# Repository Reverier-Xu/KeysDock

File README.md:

# 

The hall-effect powered, high performance, feature riched keyboard!

> [!WARNING]
> **STILL IN EARLY DEVELOPMENT!**
>
> - [ ] PCB design
> - [ ] Suitkit design
> - [ ] Firmware
> - [ ] Software
> - [ ] Extended external controllers

## Keys layout

KeysDock uses main dock with 80-keys ANSI layout.

## Suitkit design

Designed use [FreeCAD](https://www.freecad.org/) for 3D modeling and [QCAD](https://www.qcad.org/) for nameplate drawn.

Fonts used in design:

- [Iosevka](https://typeof.net/Iosevka/): An elegant monospace coding font;
- [Hershey Fonts](https://en.wikipedia.org/wiki/Hershey_fonts): a collection of vector fonts originally designed to be rendered using vectors on early cathode ray tube displays.

## Hardware design

Designed use [KiCAD](https://www.kicad.org/), validated on [QUCS-s](https://ra3xdh.github.io/).

- MCU and BLE/WiFi: ESP32-C6
- ADC: TLA2518
- Hall-effect sensors: SC4823S6-TR
- Magnetic switch: Gateron Low Profile Magnetic Jade Pro Switch

More component info is available under [here](hardware/docs).

> [!WARNING]
> LIMITATIONS: the extended F-keys suite do not have sleep mode, awake functions and RGB lights.
> Hall-effect keyboard requires too many I/O pins, which makes difficulty in transfer additional features to external dock.

## Firmware

Rust 1.94 is required for build firmware.

## Software

WIP...

## Credits

This project is built entirely with opensource softwares, with power of opensource RISC-V instruction-set.

- [KiCAD](https://www.kicad.org): GPLv3
- [FreeCAD](https://www.freecad.org): LGPLv2.1
- [QCAD](https://www.qcad.org): GPLv3
- [Inkscape](https://www.inkscape.org): GPLv2
- [QUCS-s](https://ra3xdh.github.io): GPLv2
- [Rust](https://www.rust-lang.org): Apache-2.0 & MIT
- [esp-rs](https://docs.espressif.com/projects/rust/): Apache-2.0 & MIT

The current keyboard scheme can roughly be regarded as an original one.

Additionally, special thanks to [LCEDA](https://lceda.cn/), some 3D component models in this project are sourced from here.

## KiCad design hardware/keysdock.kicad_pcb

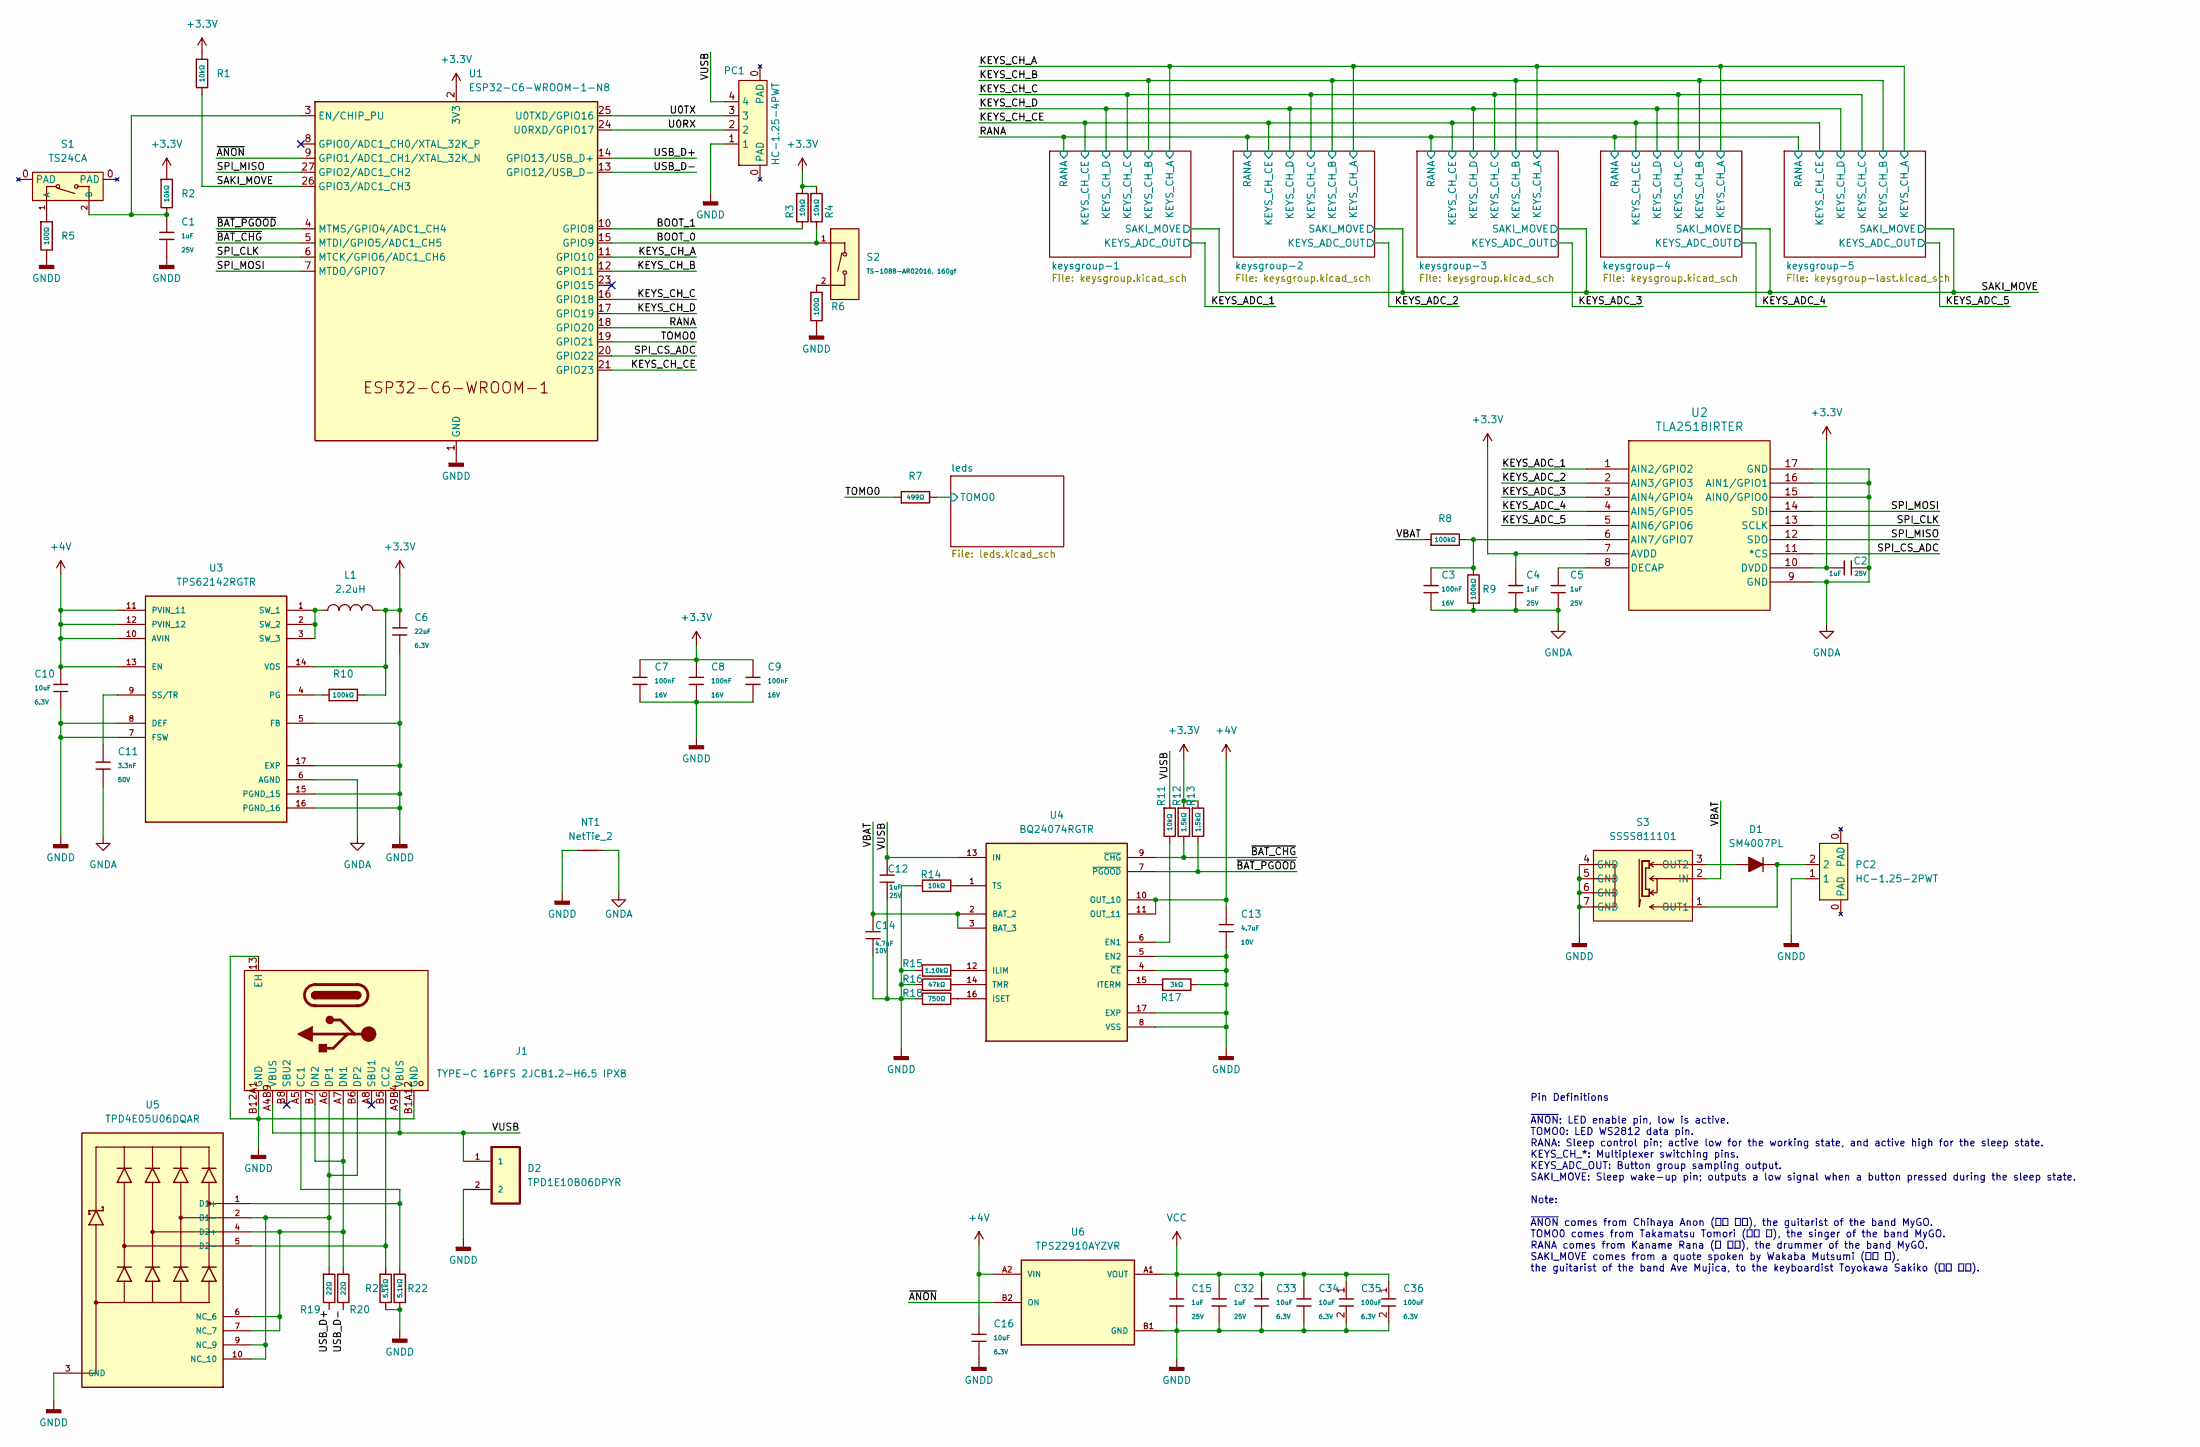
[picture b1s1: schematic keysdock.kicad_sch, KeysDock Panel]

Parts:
C1, C2, C4, C5, C12, C15, C32: 1uF; C_0402; Voltage Rated 25V; Tolerance ±10%; Part CL05A105KA5NQNC; LCSC C52923
C3, C7, C8, C9: 100nF; C_0402; Voltage Rated 16V; Tolerance ±10%; Part CL05B104KO5NNNC; LCSC C1525
C6: 22uF; C_0402; Voltage Rated 6.3V; Tolerance ±20%; Part CL05A226MQ5QUNC; LCSC C105226
C10, C16, C33, C34: 10uF; C_0402; Voltage Rated 6.3V; Tolerance ±20%; Part CL05A106MQ5NUNC; LCSC C15525
C11: 3.3nF; C_0402; Voltage Rated 50V; Tolerance ±10%; Part CL05B332KB5NNNC; LCSC C26404
C13, C14: 4.7uF; C_0402; Voltage Rated 10V; Tolerance ±20%; Part CL05A475MP5NRNC; LCSC C23733
C35, C36: 100uF; C_1206; Voltage Rated 6.3V; Manufacturer_Part_Number CL31A107MQHNNNE; Mouser Part Number 187-CL31A107MQHNNNE
D1: SM4007PL; D_SOD-123FL; LCSC C78741
D2: TPD1E10B06DPYR; DIO_TPD1E05U06DPYR; LCSC C48260
J1: TYPE-C 16PFS 2JCB1.2-H6.5 IPX8; USB-C-SMD_SHOUHAN_TYPE-C-16PFS-2JCB1.2-H6.5; Current Rating - Power 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 3A; LCSC C3020046
L1: 2.2uH; IND-SMD_L2.5-W2.0_MHCHL2520; Tolerance ±20%; LCSC C5832372
NT1: NetTie_2; NetTie-2_THT_Pad1.0mm
PC1: HC-1.25-4PWT; LCSC C2845381
PC2: HC-1.25-2PWT; LCSC C2845379
R1, R2, R3, R4, R11, R14: 10kΩ; R_0402; Overload Voltage (Max) 50V; Tolerance ±1%; Part 0402WGF1002TCE; LCSC C25744
R5, R6: 100Ω; R_0402; Overload Voltage (Max) 50V; Tolerance ±1%; Part 0402WGF1000TCE; LCSC C25076
R7: 499Ω; R_0402; Overload Voltage (Max) 50V; Tolerance ±1%; Part 0402WGF4990TCE; LCSC C4125
R8, R9, R10: 100kΩ; R_0402; Overload Voltage (Max) 50V; Tolerance ±1%; Part 0402WGF1003TCE; LCSC C25741
R12, R13: 1.5kΩ; R_0402; Overload Voltage (Max) 50V; Tolerance ±1%; Part 0402WGF1501TCE; LCSC C25867
R15: 1.10kΩ; R_0402; Overload Voltage (Max) 50V; Tolerance ±1%; Part 0402WGF1101TCE; LCSC C25860
R16: 47kΩ; R_0402; Overload Voltage (Max) 50V; Tolerance ±1%; Part 0402WGF4702TCE; LCSC C25792
R17: 3kΩ; R_0402; Overload Voltage (Max) 50V; Tolerance ±1%; Part 0402WGF3001TCE; LCSC C25784
R18: 750Ω; R_0402; Overload Voltage (Max) 50V; Tolerance ±1%; Part 0402WGF7500TCE; LCSC C25132
R19, R20: 22Ω; R_0402; Overload Voltage (Max) 50V; Tolerance ±1%; Part 0402WGF220JTCE; LCSC C25092
R21, R22: 5.1kΩ; R_0402; Overload Voltage (Max) 50V; Tolerance ±1%; Part 0402WGJ0512TCE; LCSC C25941
S1: TS24CA; LCSC C393942
S2: TS-1088-AR02016, 160gf; SW_TS-1088-AR02016; Voltage Rating (Dc) 12V; Part TS-1088-AR02016; LCSC C720477
S3: SSSS811101; SW-SMD_SSSS811101; LCSC C109335
U1: ESP32-C6-WROOM-1-N8; ESP32-C6-WROOM-1
U2: TLA2518IRTER; QFN50P300X300X80-17N; LCSC C1855741
U3: TPS62142RGTR; QFN50P300X300X80-17N; PARTREV E; LCSC C129331
U4: BQ24074RGTR; QFN50P300X300X80-17N; PARTREV M; LCSC C54313
U5: TPD4E05U06DQAR; IC_TPD4E05U06DQAR; PARTREV N; LCSC C138714
U6: TPS22910AYZVR; BGA4N50P2X2_88X88X50N; PARTREV F; LCSC C205966

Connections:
+3.3V: C2.1, C4.1, C6.1, C7.1, C8.1, C9.1, L1.2, R1.1, R2.1, R3.1, R4.1, R10.2, R12.1, R13.1, U1.2 (3V3), U2.7 (AVDD), U2.10 (DVDD), U3.14 (VOS); also elsewhere on the board
+4V: C10.1, C13.1, C16.1, U3.10 (AVIN), U3.11 (PVIN_11), U3.12 (PVIN_12), U3.13 (EN), U4.10 (OUT_10), U4.11 (OUT_11), U6.A2 (VIN)
/BOOT_0: R4.2, S2.1 (A), U1.15 (GPIO9)
/BOOT_1: R3.2, U1.10 (GPIO8)
/KEYS_ADC_1: U2.1 (AIN2/GPIO2); also elsewhere on the board
/KEYS_ADC_2: U2.2 (AIN3/GPIO3); also elsewhere on the board
/KEYS_ADC_3: U2.3 (AIN4/GPIO4); also elsewhere on the board
/KEYS_ADC_4: U2.4 (AIN5/GPIO5); also elsewhere on the board
/KEYS_ADC_5: U2.5 (AIN6/GPIO6); also elsewhere on the board
/KEYS_CH_A: U1.11 (GPIO10); also elsewhere on the board
/KEYS_CH_B: U1.12 (GPIO11); also elsewhere on the board
/KEYS_CH_C: U1.16 (GPIO18); also elsewhere on the board
/KEYS_CH_CE: U1.21 (GPIO23); also elsewhere on the board
/KEYS_CH_D: U1.17 (GPIO19); also elsewhere on the board
/RANA: U1.18 (GPIO20); also elsewhere on the board
/SAKI_MOVE: R1.2, U1.26 (GPIO3/ADC1_CH3); also elsewhere on the board
/SPI_CLK: U1.6 (MTCK/GPIO6/ADC1_CH6), U2.13 (SCLK)
/SPI_CS_ADC: U1.20 (GPIO22), U2.11 (*CS)
/SPI_MISO: U1.27 (GPIO2/ADC1_CH2), U2.12 (SDO)
/SPI_MOSI: U1.7 (MTDO/GPIO7), U2.14 (SDI)
/TOMO0: R7.1, U1.19 (GPIO21)
/U0RX: PC1.2, U1.24 (U0RXD/GPIO17)
/U0TX: PC1.3, U1.25 (U0TXD/GPIO16)
/USB_D+: R19.2, U1.14 (GPIO13/USB_D+)
/USB_D-: R20.2, U1.13 (GPIO12/USB_D-)
/VBAT: C14.1, R8.1, S3.2 (IN), U4.2 (BAT_2), U4.3 (BAT_3)
/VUSB: C12.1, D2.1, J1.A4B9 (VBUS), J1.A9B4 (VBUS), PC1.4, R11.1, U4.13 (IN)
/leds/TOMO0: R7.2; also elsewhere on the board
/~ANON: U1.9 (GPIO1/ADC1_CH1/XTAL_32K_N), U6.B2 (ON)
/~BAT_CHG: R12.2, U1.5 (MTDI/GPIO5/ADC1_CH5), U4.9 (~CHG)
/~BAT_PGOOD: R13.2, U1.4 (MTMS/GPIO4/ADC1_CH4), U4.7 (~PGOOD)
GNDA: C2.2, C3.2, C4.2, C5.2, C11.2, NT1.2, R9.1, U2.9 (GND), U2.15 (AIN0/GPIO0), U2.16 (AIN1/GPIO1), U2.17 (GND), U3.6 (AGND); also elsewhere on the board
GNDD: C1.2, C6.2, C7.2, C8.2, C9.2, C10.2, C12.2, C13.2, C14.2, C15.2, C16.2, C32.2, C33.2, C34.2, C35.2, C36.2, D2.2, J1.13 (EH), J1.B1A12 (GND), J1.B12A1 (GND), NT1.1, PC1.1, PC2.1, R5.2, R6.2, R14.1, R15.1, R16.1, R17.2, R18.1, R21.2, R22.2, S3.4 (GND), S3.5 (GND), S3.6 (GND), S3.7 (GND), U1.1 (GND), U1.28 (GND), U1.29 (GND), U3.5 (FB), U3.7 (FSW), U3.8 (DEF), U3.15 (PGND_15), U3.16 (PGND_16), U3.17 (EXP), U4.4 (~CE), U4.5 (EN2), U4.8 (VSS), U4.17 (EXP), U5.3 (GND), U5.8 (GND), U6.B1 (GND); also elsewhere on the board
unnamed: D1.2 (A), S3.3 (OUT2)
unnamed: D1.1 (K), PC2.2, S3.1 (OUT1)
unnamed: J1.A5 (CC1), R22.1, U5.1 (D1+)
unnamed: J1.B5 (CC2), R21.1, U5.5 (D2-)
unnamed: J1.A7 (DN1), J1.B7 (DN2), R20.1, U5.4 (D2+), U5.6 (NC_6), U5.7 (NC_7)
unnamed: J1.A6 (DP1), J1.B6 (DP2), R19.1, U5.2 (D1-), U5.9 (NC_9), U5.10 (NC_10)
unnamed: R5.1, S1.1 (A)
unnamed: C1.1, R2.2, S1.2 (B), U1.3 (EN/CHIP_PU)
unnamed: R6.1, S2.2 (B)
unnamed: C3.1, R8.2, R9.2, U2.6 (AIN7/GPIO7)
unnamed: C5.1, U2.8 (DECAP)
unnamed: R10.1, U3.4 (PG)
unnamed: C11.1, U3.9 (SS/TR)
unnamed: L1.1, U3.1 (SW_1), U3.2 (SW_2), U3.3 (SW_3)
unnamed: R11.2, U4.6 (EN1)
unnamed: R15.2, U4.12 (ILIM)
unnamed: R18.2, U4.16 (ISET)
unnamed: R17.1, U4.15 (ITERM)
unnamed: R16.2, U4.14 (TMR)
unnamed: R14.2, U4.1 (TS)
VCC: C15.1, C32.1, C33.1, C34.1, C35.1, C36.1, U6.A1 (VOUT); also elsewhere on the board

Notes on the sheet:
Pin Definitions ~{ANON}: LED enable pin, low is active. TOMO0: LED WS2812 data pin. RANA: Sleep control pin; active low for the working state, and active high for the sleep state. KEYS_CH_*: Multiplexer switching pins. KEYS_ADC_OUT: Button group sampling output. SAKI_MOVE: Sleep wake-up pin; output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

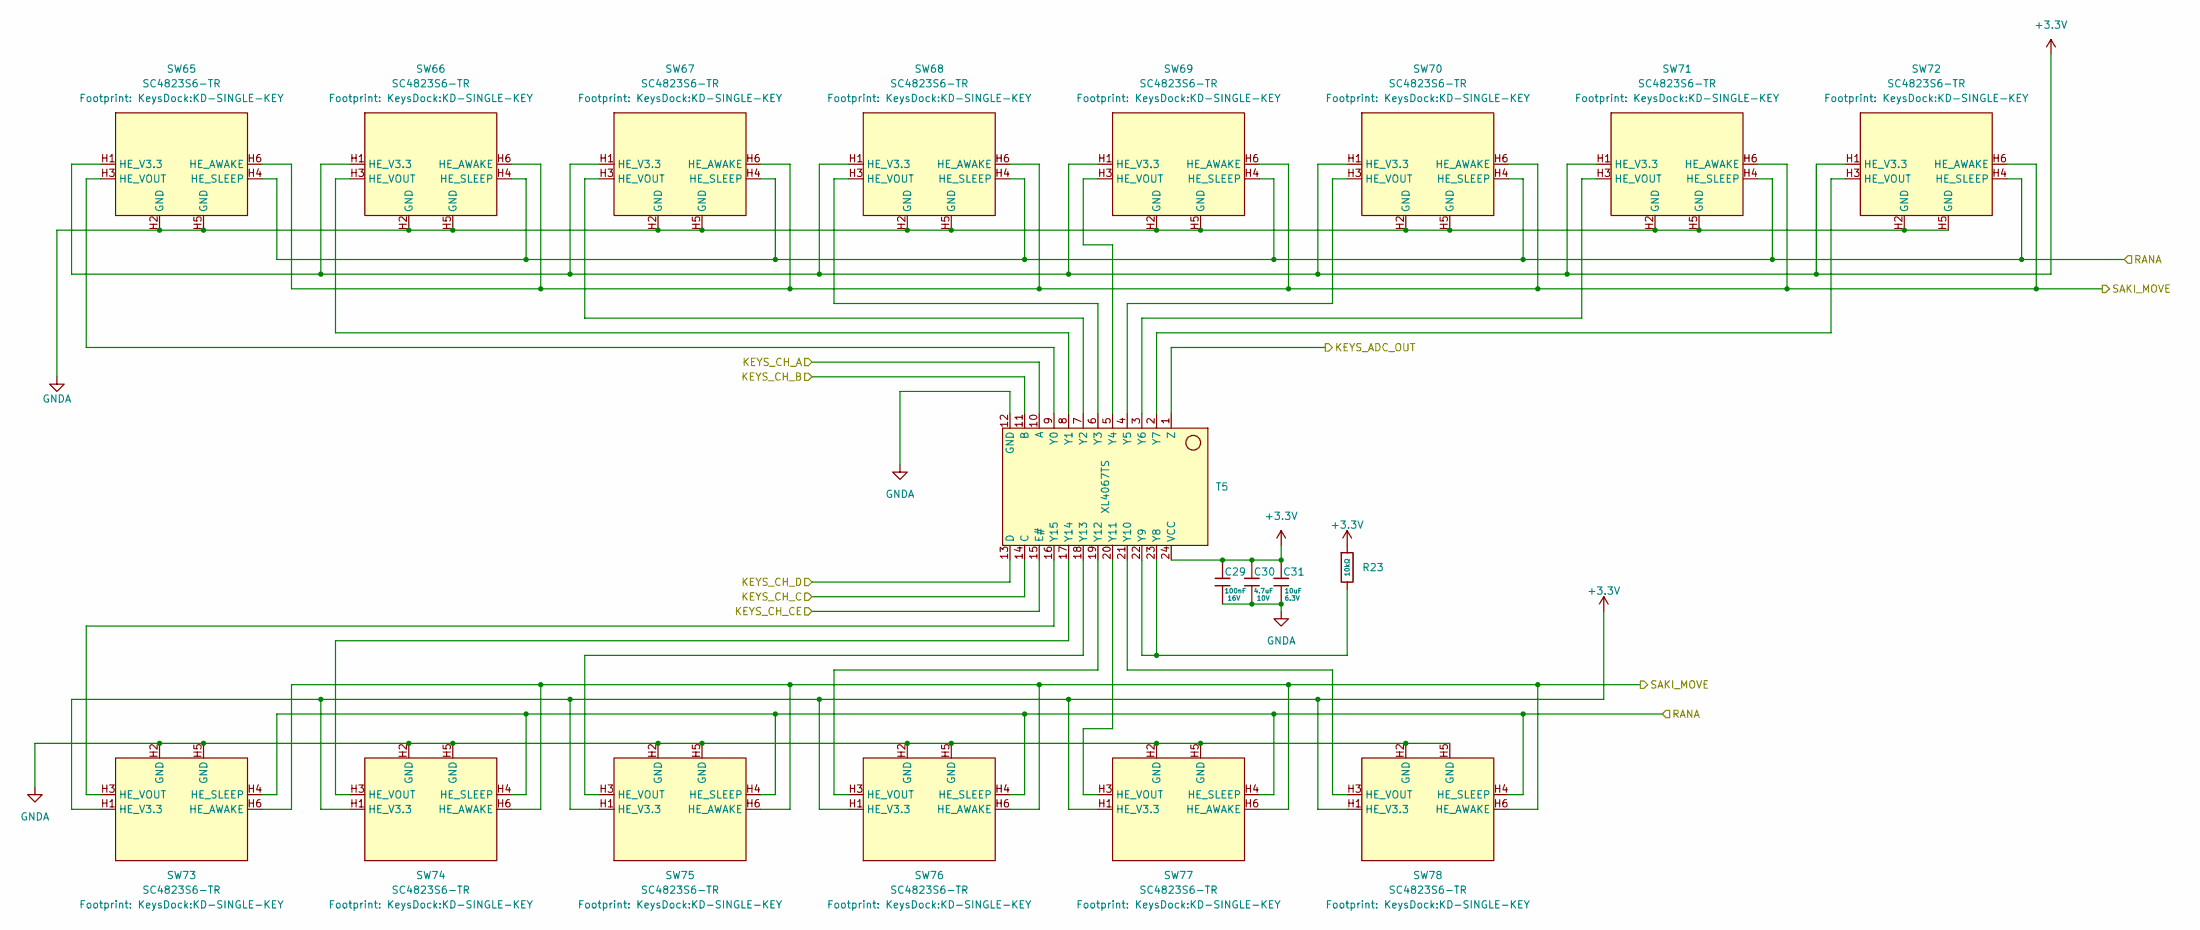
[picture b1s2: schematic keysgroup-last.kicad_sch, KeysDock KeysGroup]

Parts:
C29: 100nF; C_0402; Voltage Rated 16V; Tolerance ±10%; Part CL05B104KO5NNNC; LCSC C1525
C30: 4.7uF; C_0402; Voltage Rated 10V; Tolerance ±20%; Part CL05A475MP5NRNC; LCSC C23733
C31: 10uF; C_0402; Voltage Rated 6.3V; Tolerance ±20%; Part CL05A106MQ5NUNC; LCSC C15525
R23: 10kΩ; R_0402; Overload Voltage (Max) 50V; Tolerance ±1%; Part 0402WGF1002TCE; LCSC C25744
SW65, SW66, SW67, SW68, SW69, SW70, SW71, SW72, SW73, SW74, SW75, SW76, SW77, SW78: SC4823S6-TR; KD-SINGLE-KEY; LCSC C52021064
T5: XL4067TS; LCSC C41427445

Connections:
+3.3V: C29.1, C30.1, C31.1, R23.1, SW65.H1 (HE_V3.3), SW66.H1 (HE_V3.3), SW67.H1 (HE_V3.3), SW68.H1 (HE_V3.3), SW69.H1 (HE_V3.3), SW70.H1 (HE_V3.3), SW71.H1 (HE_V3.3), SW72.H1 (HE_V3.3), SW73.H1 (HE_V3.3), SW74.H1 (HE_V3.3), SW75.H1 (HE_V3.3), SW76.H1 (HE_V3.3), SW77.H1 (HE_V3.3), SW78.H1 (HE_V3.3), T5.24 (VCC); also elsewhere on the board
/KEYS_ADC_5: T5.1 (Z); also elsewhere on the board
/KEYS_CH_A: T5.10 (A); also elsewhere on the board
/KEYS_CH_B: T5.11 (B); also elsewhere on the board
/KEYS_CH_C: T5.14 (C); also elsewhere on the board
/KEYS_CH_CE: T5.15 (E#); also elsewhere on the board
/KEYS_CH_D: T5.13 (D); also elsewhere on the board
/RANA: SW65.H4 (HE_SLEEP), SW66.H4 (HE_SLEEP), SW67.H4 (HE_SLEEP), SW68.H4 (HE_SLEEP), SW69.H4 (HE_SLEEP), SW70.H4 (HE_SLEEP), SW71.H4 (HE_SLEEP), SW72.H4 (HE_SLEEP), SW73.H4 (HE_SLEEP), SW74.H4 (HE_SLEEP), SW75.H4 (HE_SLEEP), SW76.H4 (HE_SLEEP), SW77.H4 (HE_SLEEP), SW78.H4 (HE_SLEEP); also elsewhere on the board
/SAKI_MOVE: SW65.H6 (HE_AWAKE), SW66.H6 (HE_AWAKE), SW67.H6 (HE_AWAKE), SW68.H6 (HE_AWAKE), SW69.H6 (HE_AWAKE), SW70.H6 (HE_AWAKE), SW71.H6 (HE_AWAKE), SW72.H6 (HE_AWAKE), SW73.H6 (HE_AWAKE), SW74.H6 (HE_AWAKE), SW75.H6 (HE_AWAKE), SW76.H6 (HE_AWAKE), SW77.H6 (HE_AWAKE), SW78.H6 (HE_AWAKE); also elsewhere on the board
GNDA: C29.2, C30.2, C31.2, SW65.H2 (GND), SW65.H5 (GND), SW66.H2 (GND), SW66.H5 (GND), SW67.H2 (GND), SW67.H5 (GND), SW68.H2 (GND), SW68.H5 (GND), SW69.H2 (GND), SW69.H5 (GND), SW70.H2 (GND), SW70.H5 (GND), SW71.H2 (GND), SW71.H5 (GND), SW72.H2 (GND), SW72.H5 (GND), SW73.H2 (GND), SW73.H5 (GND), SW74.H2 (GND), SW74.H5 (GND), SW75.H2 (GND), SW75.H5 (GND), SW76.H2 (GND), SW76.H5 (GND), SW77.H2 (GND), SW77.H5 (GND), SW78.H2 (GND), SW78.H5 (GND), T5.12 (GND); also elsewhere on the board
unnamed: SW65.H3 (HE_VOUT), T5.9 (Y0)
unnamed: SW66.H3 (HE_VOUT), T5.8 (Y1)
unnamed: SW67.H3 (HE_VOUT), T5.7 (Y2)
unnamed: SW68.H3 (HE_VOUT), T5.6 (Y3)
unnamed: SW69.H3 (HE_VOUT), T5.5 (Y4)
unnamed: SW70.H3 (HE_VOUT), T5.4 (Y5)
unnamed: SW71.H3 (HE_VOUT), T5.3 (Y6)
unnamed: SW72.H3 (HE_VOUT), T5.2 (Y7)
unnamed: SW73.H3 (HE_VOUT), T5.16 (Y15)
unnamed: SW74.H3 (HE_VOUT), T5.17 (Y14)
unnamed: SW75.H3 (HE_VOUT), T5.18 (Y13)
unnamed: SW76.H3 (HE_VOUT), T5.19 (Y12)
unnamed: SW77.H3 (HE_VOUT), T5.20 (Y11)
unnamed: SW78.H3 (HE_VOUT), T5.21 (Y10)
unnamed: R23.2, T5.22 (Y9), T5.23 (Y8)

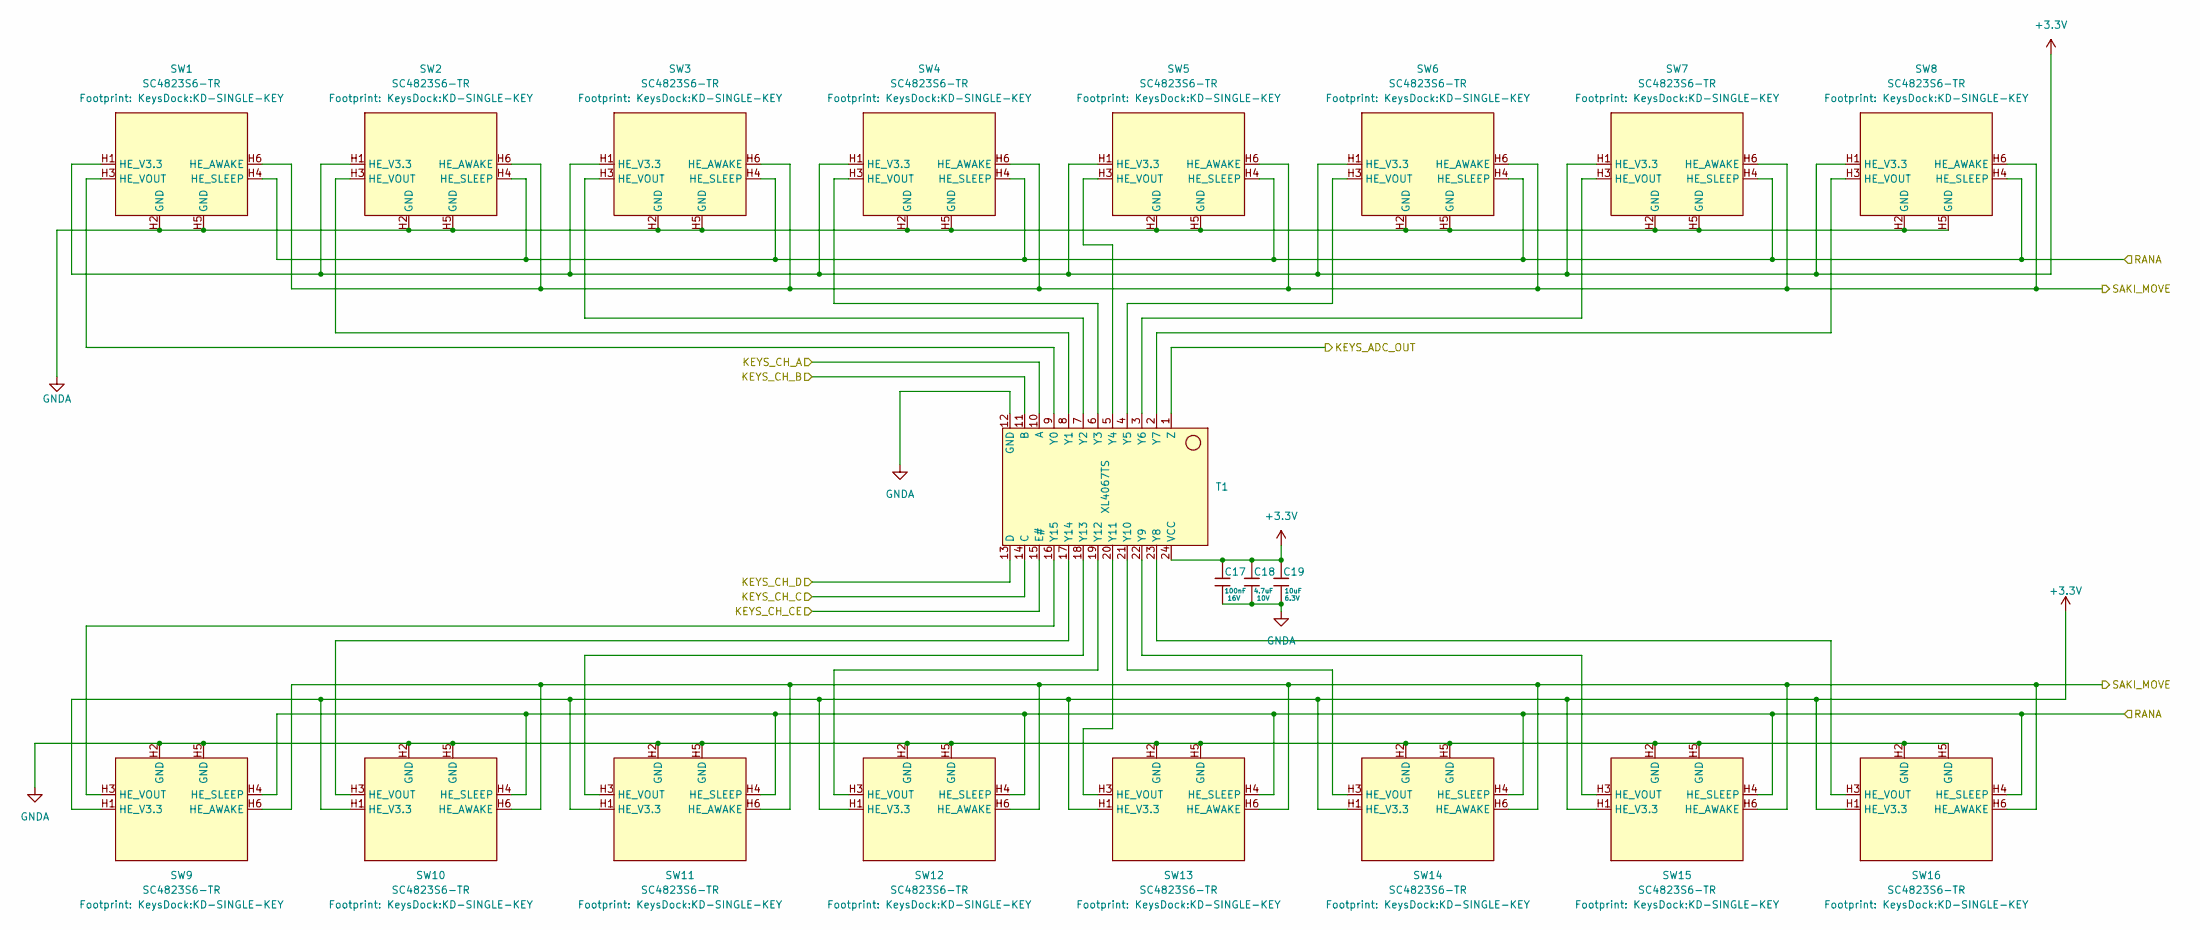
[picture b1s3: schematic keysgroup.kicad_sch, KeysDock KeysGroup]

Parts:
C17: 100nF; C_0402; Voltage Rated 16V; Tolerance ±10%; Part CL05B104KO5NNNC; LCSC C1525
C18: 4.7uF; C_0402; Voltage Rated 10V; Tolerance ±20%; Part CL05A475MP5NRNC; LCSC C23733
C19: 10uF; C_0402; Voltage Rated 6.3V; Tolerance ±20%; Part CL05A106MQ5NUNC; LCSC C15525
SW1, SW2, SW3, SW4, SW5, SW6, SW7, SW8, SW9, SW10, SW11, SW12, SW13, SW14, SW15, SW16: SC4823S6-TR; KD-SINGLE-KEY; LCSC C52021064
T1: XL4067TS; LCSC C41427445

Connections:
+3.3V: C17.1, C18.1, C19.1, SW1.H1 (HE_V3.3), SW2.H1 (HE_V3.3), SW3.H1 (HE_V3.3), SW4.H1 (HE_V3.3), SW5.H1 (HE_V3.3), SW6.H1 (HE_V3.3), SW7.H1 (HE_V3.3), SW8.H1 (HE_V3.3), SW9.H1 (HE_V3.3), SW10.H1 (HE_V3.3), SW11.H1 (HE_V3.3), SW12.H1 (HE_V3.3), SW13.H1 (HE_V3.3), SW14.H1 (HE_V3.3), SW15.H1 (HE_V3.3), SW16.H1 (HE_V3.3), T1.24 (VCC); also elsewhere on the board
/KEYS_ADC_1: T1.1 (Z); also elsewhere on the board
/KEYS_CH_A: T1.10 (A); also elsewhere on the board
/KEYS_CH_B: T1.11 (B); also elsewhere on the board
/KEYS_CH_C: T1.14 (C); also elsewhere on the board
/KEYS_CH_CE: T1.15 (E#); also elsewhere on the board
/KEYS_CH_D: T1.13 (D); also elsewhere on the board
/RANA: SW1.H4 (HE_SLEEP), SW2.H4 (HE_SLEEP), SW3.H4 (HE_SLEEP), SW4.H4 (HE_SLEEP), SW5.H4 (HE_SLEEP), SW6.H4 (HE_SLEEP), SW7.H4 (HE_SLEEP), SW8.H4 (HE_SLEEP), SW9.H4 (HE_SLEEP), SW10.H4 (HE_SLEEP), SW11.H4 (HE_SLEEP), SW12.H4 (HE_SLEEP), SW13.H4 (HE_SLEEP), SW14.H4 (HE_SLEEP), SW15.H4 (HE_SLEEP), SW16.H4 (HE_SLEEP); also elsewhere on the board
/SAKI_MOVE: SW1.H6 (HE_AWAKE), SW2.H6 (HE_AWAKE), SW3.H6 (HE_AWAKE), SW4.H6 (HE_AWAKE), SW5.H6 (HE_AWAKE), SW6.H6 (HE_AWAKE), SW7.H6 (HE_AWAKE), SW8.H6 (HE_AWAKE), SW9.H6 (HE_AWAKE), SW10.H6 (HE_AWAKE), SW11.H6 (HE_AWAKE), SW12.H6 (HE_AWAKE), SW13.H6 (HE_AWAKE), SW14.H6 (HE_AWAKE), SW15.H6 (HE_AWAKE), SW16.H6 (HE_AWAKE); also elsewhere on the board
GNDA: C17.2, C18.2, C19.2, SW1.H2 (GND), SW1.H5 (GND), SW2.H2 (GND), SW2.H5 (GND), SW3.H2 (GND), SW3.H5 (GND), SW4.H2 (GND), SW4.H5 (GND), SW5.H2 (GND), SW5.H5 (GND), SW6.H2 (GND), SW6.H5 (GND), SW7.H2 (GND), SW7.H5 (GND), SW8.H2 (GND), SW8.H5 (GND), SW9.H2 (GND), SW9.H5 (GND), SW10.H2 (GND), SW10.H5 (GND), SW11.H2 (GND), SW11.H5 (GND), SW12.H2 (GND), SW12.H5 (GND), SW13.H2 (GND), SW13.H5 (GND), SW14.H2 (GND), SW14.H5 (GND), SW15.H2 (GND), SW15.H5 (GND), SW16.H2 (GND), SW16.H5 (GND), T1.12 (GND); also elsewhere on the board
unnamed: SW1.H3 (HE_VOUT), T1.9 (Y0)
unnamed: SW2.H3 (HE_VOUT), T1.8 (Y1)
unnamed: SW3.H3 (HE_VOUT), T1.7 (Y2)
unnamed: SW4.H3 (HE_VOUT), T1.6 (Y3)
unnamed: SW5.H3 (HE_VOUT), T1.5 (Y4)
unnamed: SW6.H3 (HE_VOUT), T1.4 (Y5)
unnamed: SW7.H3 (HE_VOUT), T1.3 (Y6)
unnamed: SW8.H3 (HE_VOUT), T1.2 (Y7)
unnamed: SW9.H3 (HE_VOUT), T1.16 (Y15)
unnamed: SW10.H3 (HE_VOUT), T1.17 (Y14)
unnamed: SW11.H3 (HE_VOUT), T1.18 (Y13)
unnamed: SW12.H3 (HE_VOUT), T1.19 (Y12)
unnamed: SW13.H3 (HE_VOUT), T1.20 (Y11)
unnamed: SW14.H3 (HE_VOUT), T1.21 (Y10)
unnamed: SW15.H3 (HE_VOUT), T1.22 (Y9)
unnamed: SW16.H3 (HE_VOUT), T1.23 (Y8)

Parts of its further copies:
C20, C23, C26: 100nF; C_0402; Voltage Rated 16V; Tolerance ±10%; Part CL05B104KO5NNNC; LCSC C1525
C21, C24, C27: 4.7uF; C_0402; Voltage Rated 10V; Tolerance ±20%; Part CL05A475MP5NRNC; LCSC C23733
C22, C25, C28: 10uF; C_0402; Voltage Rated 6.3V; Tolerance ±20%; Part CL05A106MQ5NUNC; LCSC C15525
SW17, SW18, SW19, SW20, SW21, SW22, SW23, SW24, SW25, SW26, SW27, SW28, SW29, SW30, SW31, SW32, SW33, SW34, SW35, SW36, SW37, SW38, SW39, SW40, SW41, SW42, SW43, SW44, SW45, SW46, SW47, SW48, SW49, SW50, SW51, SW52, SW53, SW54, SW55, SW56, SW57, SW58, SW59, SW60, SW61, SW62, SW63, SW64: SC4823S6-TR; KD-SINGLE-KEY; LCSC C52021064
T2, T3, T4: XL4067TS; LCSC C41427445

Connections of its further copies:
+3.3V: C20.1, C21.1, C22.1, C23.1, C24.1, C25.1, C26.1, C27.1, C28.1, SW17.H1 (HE_V3.3), SW18.H1 (HE_V3.3), SW19.H1 (HE_V3.3), SW20.H1 (HE_V3.3), SW21.H1 (HE_V3.3), SW22.H1 (HE_V3.3), SW23.H1 (HE_V3.3), SW24.H1 (HE_V3.3), SW25.H1 (HE_V3.3), SW26.H1 (HE_V3.3), SW27.H1 (HE_V3.3), SW28.H1 (HE_V3.3), SW29.H1 (HE_V3.3), SW30.H1 (HE_V3.3), SW31.H1 (HE_V3.3), SW32.H1 (HE_V3.3), SW33.H1 (HE_V3.3), SW34.H1 (HE_V3.3), SW35.H1 (HE_V3.3), SW36.H1 (HE_V3.3), SW37.H1 (HE_V3.3), SW38.H1 (HE_V3.3), SW39.H1 (HE_V3.3), SW40.H1 (HE_V3.3), SW41.H1 (HE_V3.3), SW42.H1 (HE_V3.3), SW43.H1 (HE_V3.3), SW44.H1 (HE_V3.3), SW45.H1 (HE_V3.3), SW46.H1 (HE_V3.3), SW47.H1 (HE_V3.3), SW48.H1 (HE_V3.3), SW49.H1 (HE_V3.3), SW50.H1 (HE_V3.3), SW51.H1 (HE_V3.3), SW52.H1 (HE_V3.3), SW53.H1 (HE_V3.3), SW54.H1 (HE_V3.3), SW55.H1 (HE_V3.3), SW56.H1 (HE_V3.3), SW57.H1 (HE_V3.3), SW58.H1 (HE_V3.3), SW59.H1 (HE_V3.3), SW60.H1 (HE_V3.3), SW61.H1 (HE_V3.3), SW62.H1 (HE_V3.3), SW63.H1 (HE_V3.3), SW64.H1 (HE_V3.3), T2.24 (VCC), T3.24 (VCC), T4.24 (VCC); also elsewhere on the board
/KEYS_ADC_2: T2.1 (Z); also elsewhere on the board
/KEYS_ADC_3: T3.1 (Z); also elsewhere on the board
/KEYS_ADC_4: T4.1 (Z); also elsewhere on the board
/KEYS_CH_A: T2.10 (A), T3.10 (A), T4.10 (A); also elsewhere on the board
/KEYS_CH_B: T2.11 (B), T3.11 (B), T4.11 (B); also elsewhere on the board
/KEYS_CH_C: T2.14 (C), T3.14 (C), T4.14 (C); also elsewhere on the board
/KEYS_CH_CE: T2.15 (E#), T3.15 (E#), T4.15 (E#); also elsewhere on the board
/KEYS_CH_D: T2.13 (D), T3.13 (D), T4.13 (D); also elsewhere on the board
/RANA: SW17.H4 (HE_SLEEP), SW18.H4 (HE_SLEEP), SW19.H4 (HE_SLEEP), SW20.H4 (HE_SLEEP), SW21.H4 (HE_SLEEP), SW22.H4 (HE_SLEEP), SW23.H4 (HE_SLEEP), SW24.H4 (HE_SLEEP), SW25.H4 (HE_SLEEP), SW26.H4 (HE_SLEEP), SW27.H4 (HE_SLEEP), SW28.H4 (HE_SLEEP), SW29.H4 (HE_SLEEP), SW30.H4 (HE_SLEEP), SW31.H4 (HE_SLEEP), SW32.H4 (HE_SLEEP), SW33.H4 (HE_SLEEP), SW34.H4 (HE_SLEEP), SW35.H4 (HE_SLEEP), SW36.H4 (HE_SLEEP), SW37.H4 (HE_SLEEP), SW38.H4 (HE_SLEEP), SW39.H4 (HE_SLEEP), SW40.H4 (HE_SLEEP), SW41.H4 (HE_SLEEP), SW42.H4 (HE_SLEEP), SW43.H4 (HE_SLEEP), SW44.H4 (HE_SLEEP), SW45.H4 (HE_SLEEP), SW46.H4 (HE_SLEEP), SW47.H4 (HE_SLEEP), SW48.H4 (HE_SLEEP), SW49.H4 (HE_SLEEP), SW50.H4 (HE_SLEEP), SW51.H4 (HE_SLEEP), SW52.H4 (HE_SLEEP), SW53.H4 (HE_SLEEP), SW54.H4 (HE_SLEEP), SW55.H4 (HE_SLEEP), SW56.H4 (HE_SLEEP), SW57.H4 (HE_SLEEP), SW58.H4 (HE_SLEEP), SW59.H4 (HE_SLEEP), SW60.H4 (HE_SLEEP), SW61.H4 (HE_SLEEP), SW62.H4 (HE_SLEEP), SW63.H4 (HE_SLEEP), SW64.H4 (HE_SLEEP); also elsewhere on the board
/SAKI_MOVE: SW17.H6 (HE_AWAKE), SW18.H6 (HE_AWAKE), SW19.H6 (HE_AWAKE), SW20.H6 (HE_AWAKE), SW21.H6 (HE_AWAKE), SW22.H6 (HE_AWAKE), SW23.H6 (HE_AWAKE), SW24.H6 (HE_AWAKE), SW25.H6 (HE_AWAKE), SW26.H6 (HE_AWAKE), SW27.H6 (HE_AWAKE), SW28.H6 (HE_AWAKE), SW29.H6 (HE_AWAKE), SW30.H6 (HE_AWAKE), SW31.H6 (HE_AWAKE), SW32.H6 (HE_AWAKE), SW33.H6 (HE_AWAKE), SW34.H6 (HE_AWAKE), SW35.H6 (HE_AWAKE), SW36.H6 (HE_AWAKE), SW37.H6 (HE_AWAKE), SW38.H6 (HE_AWAKE), SW39.H6 (HE_AWAKE), SW40.H6 (HE_AWAKE), SW41.H6 (HE_AWAKE), SW42.H6 (HE_AWAKE), SW43.H6 (HE_AWAKE), SW44.H6 (HE_AWAKE), SW45.H6 (HE_AWAKE), SW46.H6 (HE_AWAKE), SW47.H6 (HE_AWAKE), SW48.H6 (HE_AWAKE), SW49.H6 (HE_AWAKE), SW50.H6 (HE_AWAKE), SW51.H6 (HE_AWAKE), SW52.H6 (HE_AWAKE), SW53.H6 (HE_AWAKE), SW54.H6 (HE_AWAKE), SW55.H6 (HE_AWAKE), SW56.H6 (HE_AWAKE), SW57.H6 (HE_AWAKE), SW58.H6 (HE_AWAKE), SW59.H6 (HE_AWAKE), SW60.H6 (HE_AWAKE), SW61.H6 (HE_AWAKE), SW62.H6 (HE_AWAKE), SW63.H6 (HE_AWAKE), SW64.H6 (HE_AWAKE); also elsewhere on the board
GNDA: C20.2, C21.2, C22.2, C23.2, C24.2, C25.2, C26.2, C27.2, C28.2, SW17.H2 (GND), SW17.H5 (GND), SW18.H2 (GND), SW18.H5 (GND), SW19.H2 (GND), SW19.H5 (GND), SW20.H2 (GND), SW20.H5 (GND), SW21.H2 (GND), SW21.H5 (GND), SW22.H2 (GND), SW22.H5 (GND), SW23.H2 (GND), SW23.H5 (GND), SW24.H2 (GND), SW24.H5 (GND), SW25.H2 (GND), SW25.H5 (GND), SW26.H2 (GND), SW26.H5 (GND), SW27.H2 (GND), SW27.H5 (GND), SW28.H2 (GND), SW28.H5 (GND), SW29.H2 (GND), SW29.H5 (GND), SW30.H2 (GND), SW30.H5 (GND), SW31.H2 (GND), SW31.H5 (GND), SW32.H2 (GND), SW32.H5 (GND), SW33.H2 (GND), SW33.H5 (GND), SW34.H2 (GND), SW34.H5 (GND), SW35.H2 (GND), SW35.H5 (GND), SW36.H2 (GND), SW36.H5 (GND), SW37.H2 (GND), SW37.H5 (GND), SW38.H2 (GND), SW38.H5 (GND), SW39.H2 (GND), SW39.H5 (GND), SW40.H2 (GND), SW40.H5 (GND), SW41.H2 (GND), SW41.H5 (GND), SW42.H2 (GND), SW42.H5 (GND), SW43.H2 (GND), SW43.H5 (GND), SW44.H2 (GND), SW44.H5 (GND), SW45.H2 (GND), SW45.H5 (GND), SW46.H2 (GND), SW46.H5 (GND), SW47.H2 (GND), SW47.H5 (GND), SW48.H2 (GND), SW48.H5 (GND), SW49.H2 (GND), SW49.H5 (GND), SW50.H2 (GND), SW50.H5 (GND), SW51.H2 (GND), SW51.H5 (GND), SW52.H2 (GND), SW52.H5 (GND), SW53.H2 (GND), SW53.H5 (GND), SW54.H2 (GND), SW54.H5 (GND), SW55.H2 (GND), SW55.H5 (GND), SW56.H2 (GND), SW56.H5 (GND), SW57.H2 (GND), SW57.H5 (GND), SW58.H2 (GND), SW58.H5 (GND), SW59.H2 (GND), SW59.H5 (GND), SW60.H2 (GND), SW60.H5 (GND), SW61.H2 (GND), SW61.H5 (GND), SW62.H2 (GND), SW62.H5 (GND), SW63.H2 (GND), SW63.H5 (GND), SW64.H2 (GND), SW64.H5 (GND), T2.12 (GND), T3.12 (GND), T4.12 (GND); also elsewhere on the board
unnamed: SW17.H3 (HE_VOUT), T2.9 (Y0)
unnamed: SW18.H3 (HE_VOUT), T2.8 (Y1)
unnamed: SW19.H3 (HE_VOUT), T2.7 (Y2)
unnamed: SW20.H3 (HE_VOUT), T2.6 (Y3)
unnamed: SW21.H3 (HE_VOUT), T2.5 (Y4)
unnamed: SW22.H3 (HE_VOUT), T2.4 (Y5)
unnamed: SW23.H3 (HE_VOUT), T2.3 (Y6)
unnamed: SW24.H3 (HE_VOUT), T2.2 (Y7)
unnamed: SW25.H3 (HE_VOUT), T2.16 (Y15)
unnamed: SW26.H3 (HE_VOUT), T2.17 (Y14)
unnamed: SW27.H3 (HE_VOUT), T2.18 (Y13)
unnamed: SW28.H3 (HE_VOUT), T2.19 (Y12)
unnamed: SW29.H3 (HE_VOUT), T2.20 (Y11)
unnamed: SW30.H3 (HE_VOUT), T2.21 (Y10)
unnamed: SW31.H3 (HE_VOUT), T2.22 (Y9)
unnamed: SW32.H3 (HE_VOUT), T2.23 (Y8)
unnamed: SW33.H3 (HE_VOUT), T3.9 (Y0)
unnamed: SW34.H3 (HE_VOUT), T3.8 (Y1)
unnamed: SW35.H3 (HE_VOUT), T3.7 (Y2)
unnamed: SW36.H3 (HE_VOUT), T3.6 (Y3)
unnamed: SW37.H3 (HE_VOUT), T3.5 (Y4)
unnamed: SW38.H3 (HE_VOUT), T3.4 (Y5)
unnamed: SW39.H3 (HE_VOUT), T3.3 (Y6)
unnamed: SW40.H3 (HE_VOUT), T3.2 (Y7)
unnamed: SW41.H3 (HE_VOUT), T3.16 (Y15)
unnamed: SW42.H3 (HE_VOUT), T3.17 (Y14)
unnamed: SW43.H3 (HE_VOUT), T3.18 (Y13)
unnamed: SW44.H3 (HE_VOUT), T3.19 (Y12)
unnamed: SW45.H3 (HE_VOUT), T3.20 (Y11)
unnamed: SW46.H3 (HE_VOUT), T3.21 (Y10)
unnamed: SW47.H3 (HE_VOUT), T3.22 (Y9)
unnamed: SW48.H3 (HE_VOUT), T3.23 (Y8)
unnamed: SW49.H3 (HE_VOUT), T4.9 (Y0)
unnamed: SW50.H3 (HE_VOUT), T4.8 (Y1)
unnamed: SW51.H3 (HE_VOUT), T4.7 (Y2)
unnamed: SW52.H3 (HE_VOUT), T4.6 (Y3)
unnamed: SW53.H3 (HE_VOUT), T4.5 (Y4)
unnamed: SW54.H3 (HE_VOUT), T4.4 (Y5)
unnamed: SW55.H3 (HE_VOUT), T4.3 (Y6)
unnamed: SW56.H3 (HE_VOUT), T4.2 (Y7)
unnamed: SW57.H3 (HE_VOUT), T4.16 (Y15)
unnamed: SW58.H3 (HE_VOUT), T4.17 (Y14)
unnamed: SW59.H3 (HE_VOUT), T4.18 (Y13)
unnamed: SW60.H3 (HE_VOUT), T4.19 (Y12)
unnamed: SW61.H3 (HE_VOUT), T4.20 (Y11)
unnamed: SW62.H3 (HE_VOUT), T4.21 (Y10)
unnamed: SW63.H3 (HE_VOUT), T4.22 (Y9)
unnamed: SW64.H3 (HE_VOUT), T4.23 (Y8)

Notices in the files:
hardware/controller.kicad_pcb:
(c) 2026 Wo0t3c Industries
hardware/keysdock.kicad_pcb:
(c) 2025-2026 keys.woooo.tech
